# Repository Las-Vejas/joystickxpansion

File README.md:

# joystickxpansion

A joystick expansion module for the Hackxpansion console.

It uses the SKRHABE010 joystick, which is a low profile joystick, since I am working with little space. Also has a click function.

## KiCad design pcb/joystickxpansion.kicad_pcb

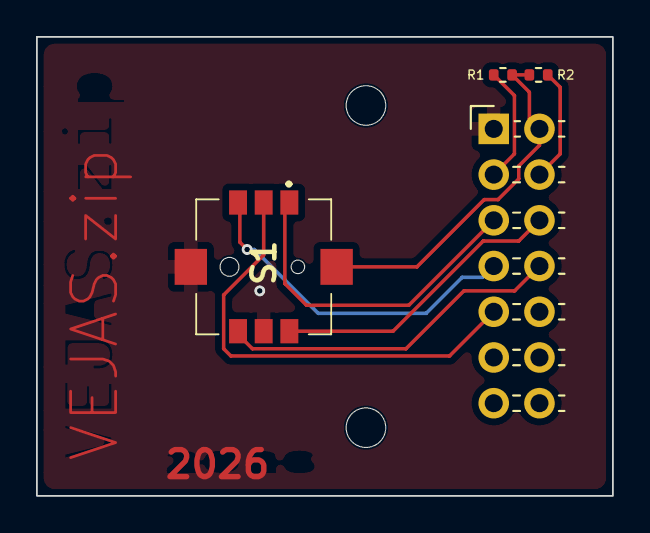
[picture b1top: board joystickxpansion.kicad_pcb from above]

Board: 2 copper layers, 32.0 x 25.5 mm, 4 parts (0 on the bottom side), 9 nets.

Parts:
J1: Male_Module
R1: 1k; R_0402_1005Metric
R2: 100k; R_0402_1005Metric
S1: SKRHABE010

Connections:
+3V3: J1.2 (3V3), R1.1, R2.1, S1.7
/J_A: J1.5 (GPIO0), S1.1 (A)
/J_B: J1.6 (GPIO1), S1.4 (B)
/J_C: J1.7 (GPI02), S1.3 (C)
/J_CENTER: J1.9 (GPIO4), S1.2 (CENTER)
/J_D: J1.8 (GPIO3), S1.6 (D)
GND: J1.1 (GND), S1.5 (COMMON), S1.8
unnamed: J1.3 (MD0), R1.2
unnamed: J1.4 (MD1), R2.2

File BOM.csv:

Reference,Qty,Price,Value,LCSC Part #
R1,1,0.15 $US,1k,C140197
R2,1,0.19 $US,100k,C2906859
S1,1,0.78 $US,SKRHABE010,C139794
PCB,5,4.00 $US,N/A,N/A
TOTAL,,5.12 $US,,

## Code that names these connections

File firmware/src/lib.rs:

#![no_std]

use xpanse_api::{
    bus::allocator::BusAllocator,
    driver::{Driver, DriverError, DriverMeta},
    gpio_bank::{BankPins, GpioBank},
    interfaces::buttons::{A, Down, Up, Left, Right, pin_button},
    metadata::{ModuleDetectResistor, ModuleID, ModuleSlot},
    registry::Registry,
};

pub struct JoystickDriver;

impl DriverMeta for JoystickDriver {
    const ID: ModuleID = ModuleID {
        md0: ModuleDetectResistor::R1K,
        md1: ModuleDetectResistor::R100K,
    };
}

impl<G: BankPins> Driver<G> for JoystickDriver {
    async fn create(
        gpio_bank: GpioBank<G>,
        slot: ModuleSlot,
        registry: &mut Registry,
        bus_allocator: &mut BusAllocator,
    ) -> Result<(), DriverError> {
        registry.register(slot, Self::ID, pin_button::<Up>(gpio_bank.gpio0.into()));
        registry.register(slot, Self::ID, pin_button::<Right>(gpio_bank.gpio1.into()));
        registry.register(slot, Self::ID, pin_button::<Down>(gpio_bank.gpio2.into()));
        registry.register(slot, Self::ID, pin_button::<Left>(gpio_bank.gpio3.into()));
        // Pressing the stick in acts as the primary action button
        registry.register(slot, Self::ID, pin_button::<A>(gpio_bank.gpio4.into()));

        // Plain GPIO inputs, no buses needed
        let _ = bus_allocator;

        Ok(())
}
}
